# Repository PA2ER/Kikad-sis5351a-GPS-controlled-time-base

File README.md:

# Kikad-sis5351a-GPS-controlled-time-base

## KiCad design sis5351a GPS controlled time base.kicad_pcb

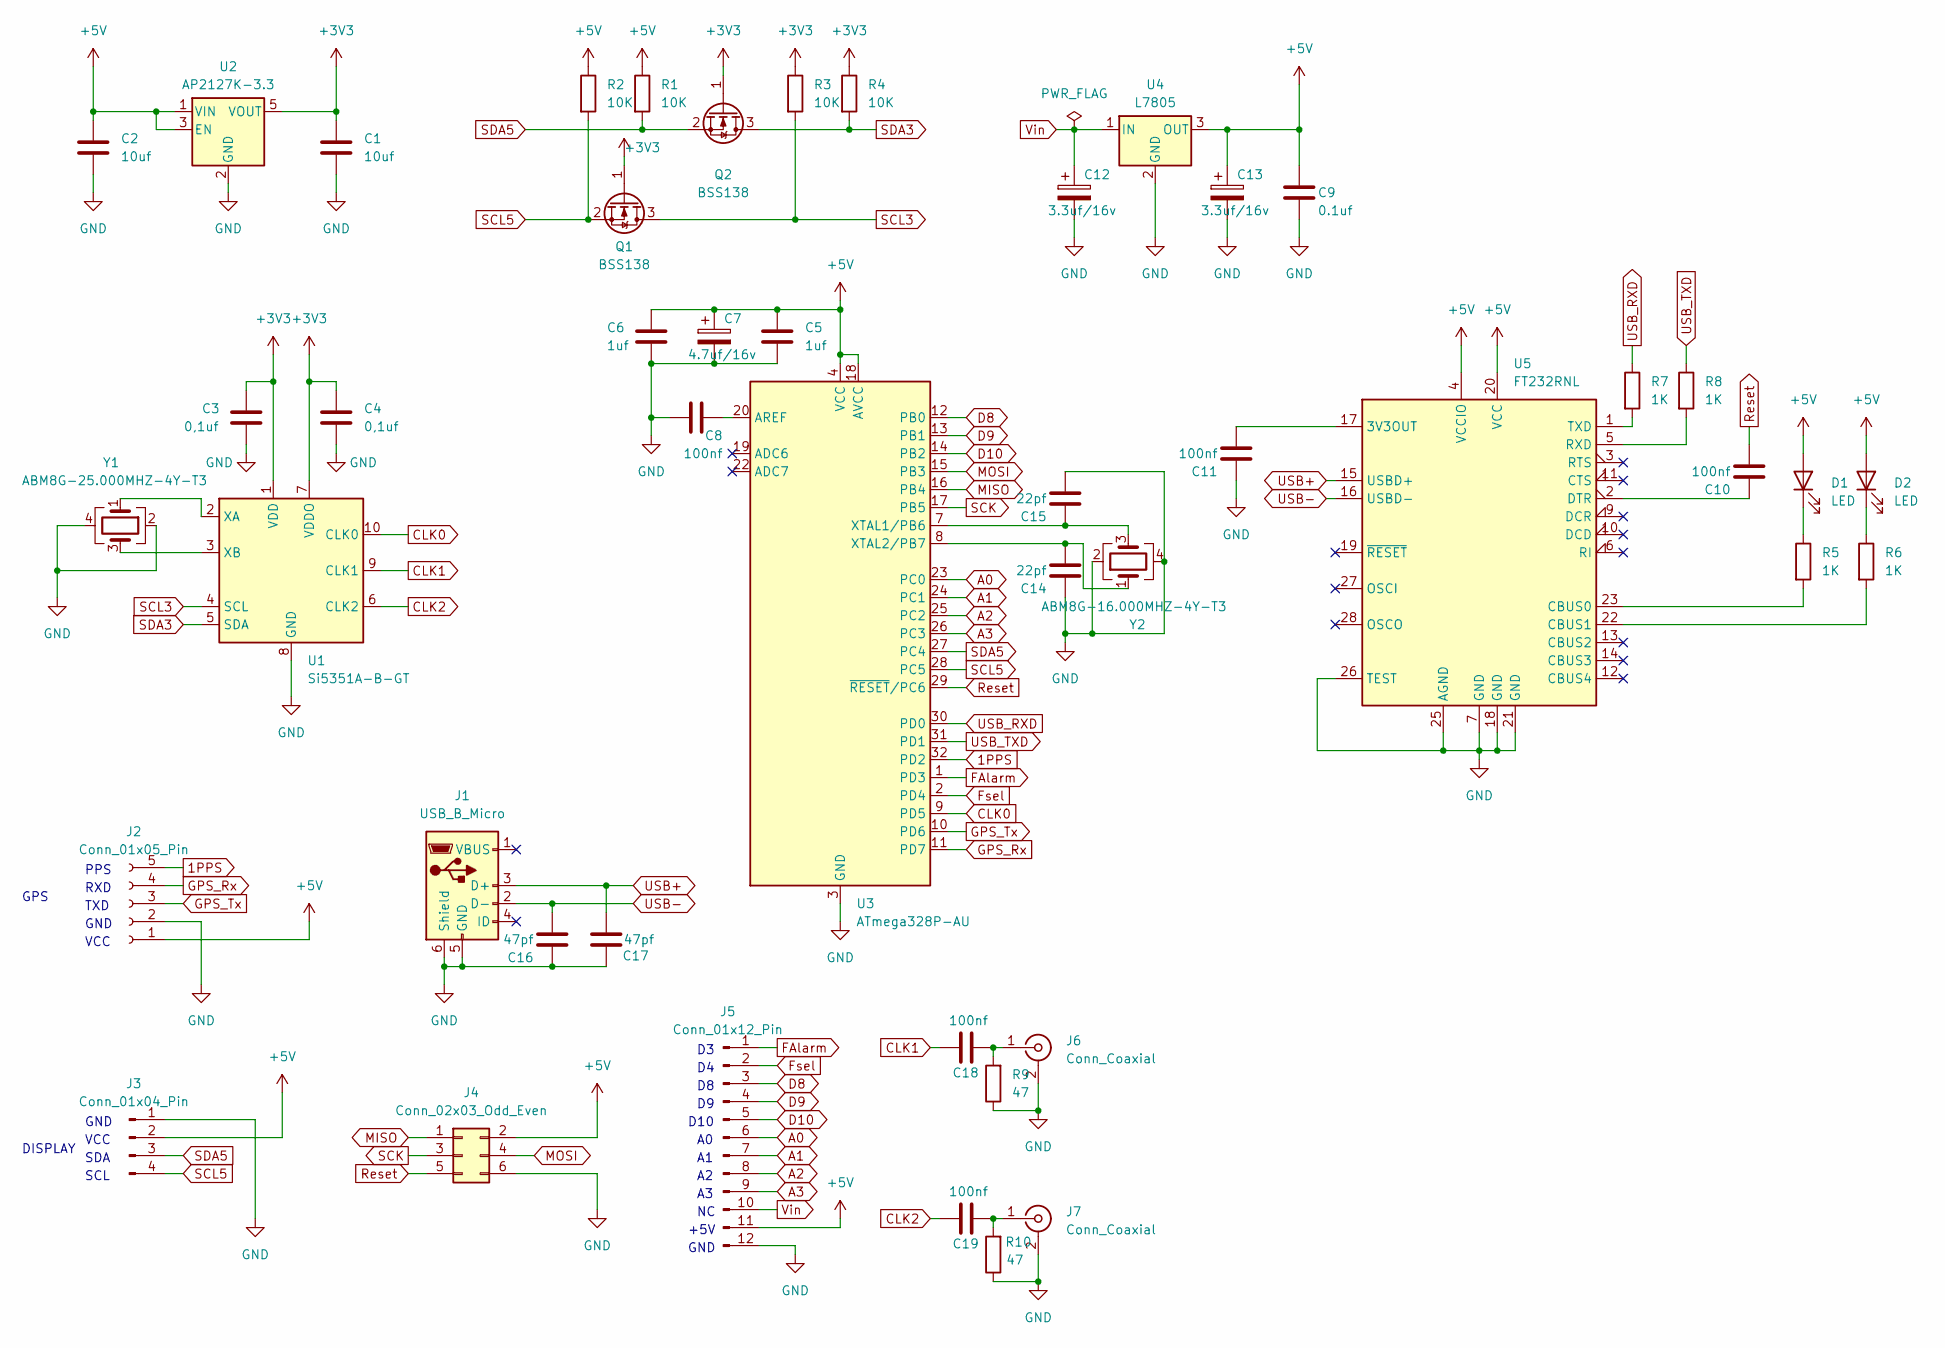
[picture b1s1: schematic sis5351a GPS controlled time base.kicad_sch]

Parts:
C1, C2: 10uf; C_0805_2012Metric_Pad1.18x1.45mm_HandSolder
C3, C4: 0,1uf; C_0805_2012Metric_Pad1.18x1.45mm_HandSolder
C5, C6: 1uf; C_0805_2012Metric_Pad1.18x1.45mm_HandSolder
C7: 4.7uf/16v; C_1206_3216Metric_Pad1.33x1.80mm_HandSolder
C8, C10, C11, C18, C19: 100nf; C_0805_2012Metric_Pad1.18x1.45mm_HandSolder
C9: 0.1uf; C_0805_2012Metric_Pad1.18x1.45mm_HandSolder
C12, C13: 3.3uf/16v; C_1206_3216Metric_Pad1.33x1.80mm_HandSolder
C14, C15: 22pf; C_0805_2012Metric_Pad1.18x1.45mm_HandSolder
C16, C17: 47pf; C_0805_2012Metric_Pad1.18x1.45mm_HandSolder
D1, D2: LED; LED_0805_2012Metric_Pad1.15x1.40mm_HandSolder
J1: USB_B_Micro; USB_Micro-B_Amphenol_10118193-0001LF_Horizontal
J2: Conn_01x05_Pin; PinSocket_1x05_P2.54mm_Vertical
J3: Conn_01x04_Pin; PinHeader_1x04_P2.54mm_Vertical
J4: Conn_02x03_Odd_Even; PinHeader_2x03_P2.54mm_Vertical
J5: Conn_01x12_Pin; PinHeader_1x12_P2.54mm_Vertical
J6, J7: Conn_Coaxial; SMA_Amphenol_901-143_Horizontal
Q1, Q2: BSS138; SOT-23
R1, R2, R3, R4: 10K; R_0805_2012Metric_Pad1.20x1.40mm_HandSolder
R5, R6, R7, R8: 1K; R_0805_2012Metric_Pad1.20x1.40mm_HandSolder
R9, R10: 47; R_0805_2012Metric_Pad1.20x1.40mm_HandSolder
U1: Si5351A-B-GT; MSOP-10_3x3mm_P0.5mm
U2: AP2127K-3.3; SOT-23-5
U3: ATmega328P-AU; TQFP-32_7x7mm_P0.8mm
U4: L7805; TO-220-3_Horizontal_TabDown
U5: FT232RNL; SSOP-28_5.3x10.2mm_P0.65mm
Y1: ABM8G-25.000MHZ-4Y-T3; Crystal_SMD_Abracon_ABM8AIG-4Pin_3.2x2.5mm
Y2: ABM8G-16.000MHZ-4Y-T3; Crystal_SMD_3225-4Pin_3.2x2.5mm_HandSoldering

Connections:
1PPS: J2.5, U3.32 (PD2)
+3V3: C1.1, C3.1, C4.1, Q1.1 (G), Q2.1 (G), R3.1, R4.1, U1.1 (VDD), U1.7 (VDDO), U2.5 (VOUT)
+5V: C2.1, C5.1, C6.1, C7.1, C9.1, C13.1, D1.2 (A), D2.2 (A), J2.1, J3.2, J4.2, J5.11, R1.1, R2.1, U2.1 (VIN), U2.3 (EN), U3.4 (VCC), U3.6 (VCC), U3.18 (AVCC), U4.3 (OUT), U5.4 (VCCIO), U5.20 (VCC)
A0: J5.6, U3.23 (PC0)
A1: J5.7, U3.24 (PC1)
A2: J5.8, U3.25 (PC2)
A3: J5.9, U3.26 (PC3)
CLK0: U1.10 (CLK0), U3.9 (PD5)
CLK1: C18.2, U1.9 (CLK1)
CLK2: C19.2, U1.6 (CLK2)
D8: J5.3, U3.12 (PB0)
D9: J5.4, U3.13 (PB1)
D10: J5.5, U3.14 (PB2)
FAlarm: J5.1, U3.1 (PD3)
Fsel: J5.2, U3.2 (PD4)
GND: C1.2, C2.2, C3.2, C4.2, C5.2, C6.2, C7.2, C8.1, C9.2, C11.1, C12.2, C13.2, C14.1, C15.2, C16.1, C17.1, J1.5 (GND), J1.6 (Shield), J2.2, J3.1, J4.6, J5.12, J6.2 (Ext), J7.2 (Ext), R9.1, R10.1, U1.8 (GND), U2.2 (GND), U3.3 (GND), U3.5 (GND), U3.21 (GND), U4.2 (GND), U5.7 (GND), U5.18 (GND), U5.21 (GND), U5.25 (AGND), U5.26 (TEST), Y1.2, Y1.4, Y2.2, Y2.4
GPS_Rx: J2.4, U3.11 (PD7)
GPS_Tx: J2.3, U3.10 (PD6)
MISO: J4.1, U3.16 (PB4)
MOSI: J4.4, U3.15 (PB3)
unnamed: D1.1 (K), R5.1
unnamed: D2.1 (K), R6.1
unnamed: C18.1, J6.1 (In), R9.2
unnamed: C19.1, J7.1 (In), R10.2
unnamed: C8.2, U3.20 (AREF)
unnamed: C15.1, U3.7 (XTAL1/PB6), Y2.3
unnamed: C14.2, U3.8 (XTAL2/PB7), Y2.1
unnamed: C11.2, U5.17 (3V3OUT)
unnamed: R5.2, U5.23 (CBUS0)
unnamed: R6.2, U5.22 (CBUS1)
unnamed: C10.1, U5.2 (DTR)
unnamed: R8.2, U5.5 (RXD)
unnamed: R7.2, U5.1 (TXD)
Reset: C10.2, J4.5, U3.29 (~RESET/PC6)
SCK: J4.3, U3.17 (PB5)
SCL3: Q1.3 (D), R3.2, U1.4 (SCL)
SCL5: J3.4, Q1.2 (S), R2.2, U3.28 (PC5)
SDA3: Q2.3 (D), R4.2, U1.5 (SDA)
SDA5: J3.3, Q2.2 (S), R1.2, U3.27 (PC4)
USB+: C17.2, J1.3 (D+), U5.15 (USBD+)
USB-: C16.2, J1.2 (D-), U5.16 (USBD-)
USB_RXD: R7.1, U3.30 (PD0)
USB_TXD: R8.1, U3.31 (PD1)
Vin: C12.1, J5.10, U4.1 (IN)

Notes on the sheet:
GND
RXD
+5V
PPS
VCC
TXD
D10
SDA
DISPLAY
GPS
SCL

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
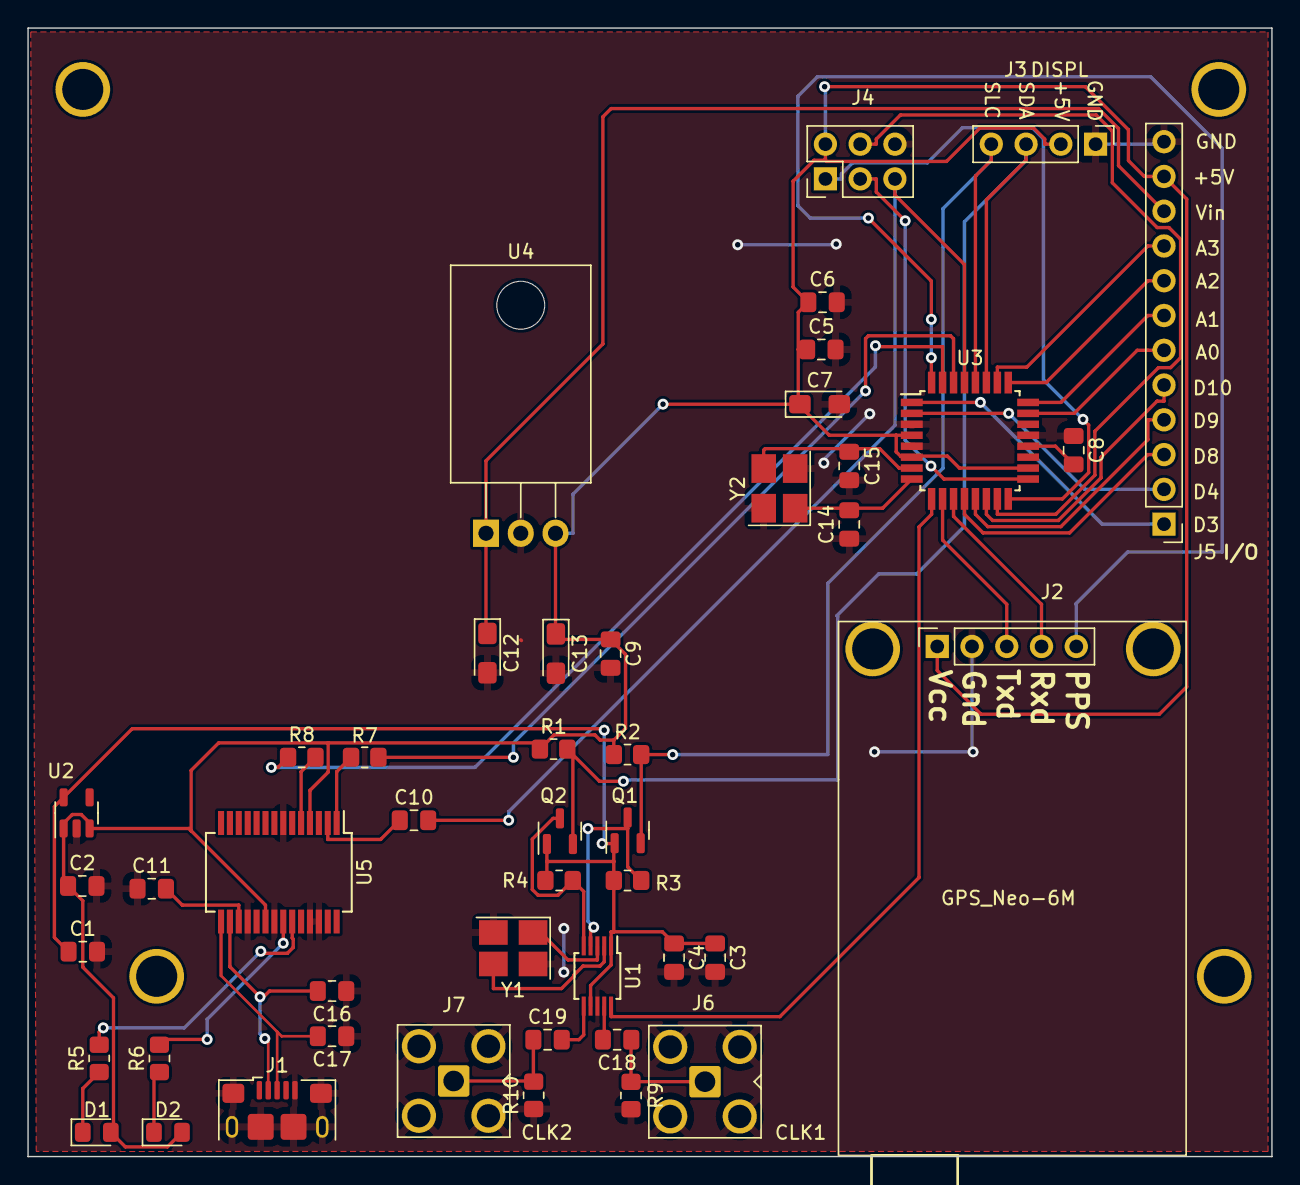
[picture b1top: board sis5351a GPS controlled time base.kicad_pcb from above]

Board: 2 copper layers, 90.9 x 82.5 mm, 47 parts (0 on the bottom side), 46 nets.

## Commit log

2024-07-04 First attemt
